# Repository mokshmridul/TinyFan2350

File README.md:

# Klipper TinyFan2350

A small Klipper fan / LED / thermistor controller based on the **Waveshare RP2350-Zero**, derived from [Gi7mo/TinyFan](https://github.com/Gi7mo/TinyFan).

|[• Build it](./Production)|[• Set it up](./Klipper)|[• Mount it](./Mount)|
|---|---|---|
|Order the PCB, parts list, soldering|Flashing, jumpers, wiring, Klipper config|Printable DIN rail mount, optional fan bridge|

## Features
- **5 fan ports** (JST-XH 4-pin) for 2-, 3- and 4-pin fans, 0.6A each
  - every fan has its own PWM output and tacho input -> independent speeds
  - per fan: mode jumper (**4P** = 4-pin PWM, **2/3** = switched GND) and voltage jumper (**VIN** or **5V**)
- **2 addressable LED ports** (JST-XH 3-pin), data level-shifted to 5V, VIN or 5V per port, 3A per connector
- **4 thermistor ports** (JST-XH 2-pin) on the RP2350 ADC
- **EXP header** with 4 free GPIOs (GP12-GP15)
- Inputs: **12/24V (VIN)** and **5V** for the fans and LEDs, each with a mini blade fuse (5A max, 3.75A continuous) and a
  reverse-polarity diode; no converters on board
- The RP2350-Zero is powered by its own **USB-C** cable, so the board cannot feed power back into the USB host
- All bottom-side SMD parts are **JLCPCB Basic** parts (cheap Economic assembly)
- 2 layers, 1 oz copper, black solder mask; SMD parts only on the bottom, THT only on the top; socketed MCU
- 100 x 65 mm, 4x M3 mounting holes (93 x 58 mm)
- Printable [DIN rail mount](./Mount) and an optional [fan bridge](./Mount#fan-bridge-optional) for a 40 mm cooling fan, run from one of the fan ports

## Files
|[Pinout](./Images/TinyFan2350_Pinout.png)|[Schematic](./Production/TinyFan2350_Schematic.pdf)|[Klipper config](./Klipper/TinyFan2350.cfg)|[KiCad project](./KiCad)|[Simulation](./Simulation)|[Pictures](./Images)|[Download](https://github.com/mokshmridul/TinyFan2350/releases/latest)|
|---|---|---|---|---|---|---|

## Notes
- Original TinyFan by [Gi7mo](https://github.com/Gi7mo/TinyFan), idea by [Rama](https://github.com/Ramalama2).
- Board revision **v1.3**: new tach inputs (series resistor, pass transistor and a capacitor at the pin instead of a
  diode), so the RP2350 sees a fan's low level properly and stays protected while a fan is switched; the unused D3
  pads are gone. See [Build it](./Production#v13-printed-on-the-board). It passes KiCad ERC/DRC and is
  simulated, but **it has not been built or tested yet**: read [Limits and safety](./Production#limits-and-safety) first.
- Release **v1.31**: the [schematic](./Production/TinyFan2350_Schematic.pdf) is redrawn on one page and is easier to
  read. The circuit and the board did not change, and the board still reads v1.3.

## License
GPL-3.0, the same as the original TinyFan. See [LICENSE](./LICENSE).

## Disclaimer
This project is provided on an "as-is" basis, without any warranty of any kind. I am not responsible for any damage, injury, loss or other issues caused by building or using it. If you choose to build or use this board, you do so entirely at your own risk.

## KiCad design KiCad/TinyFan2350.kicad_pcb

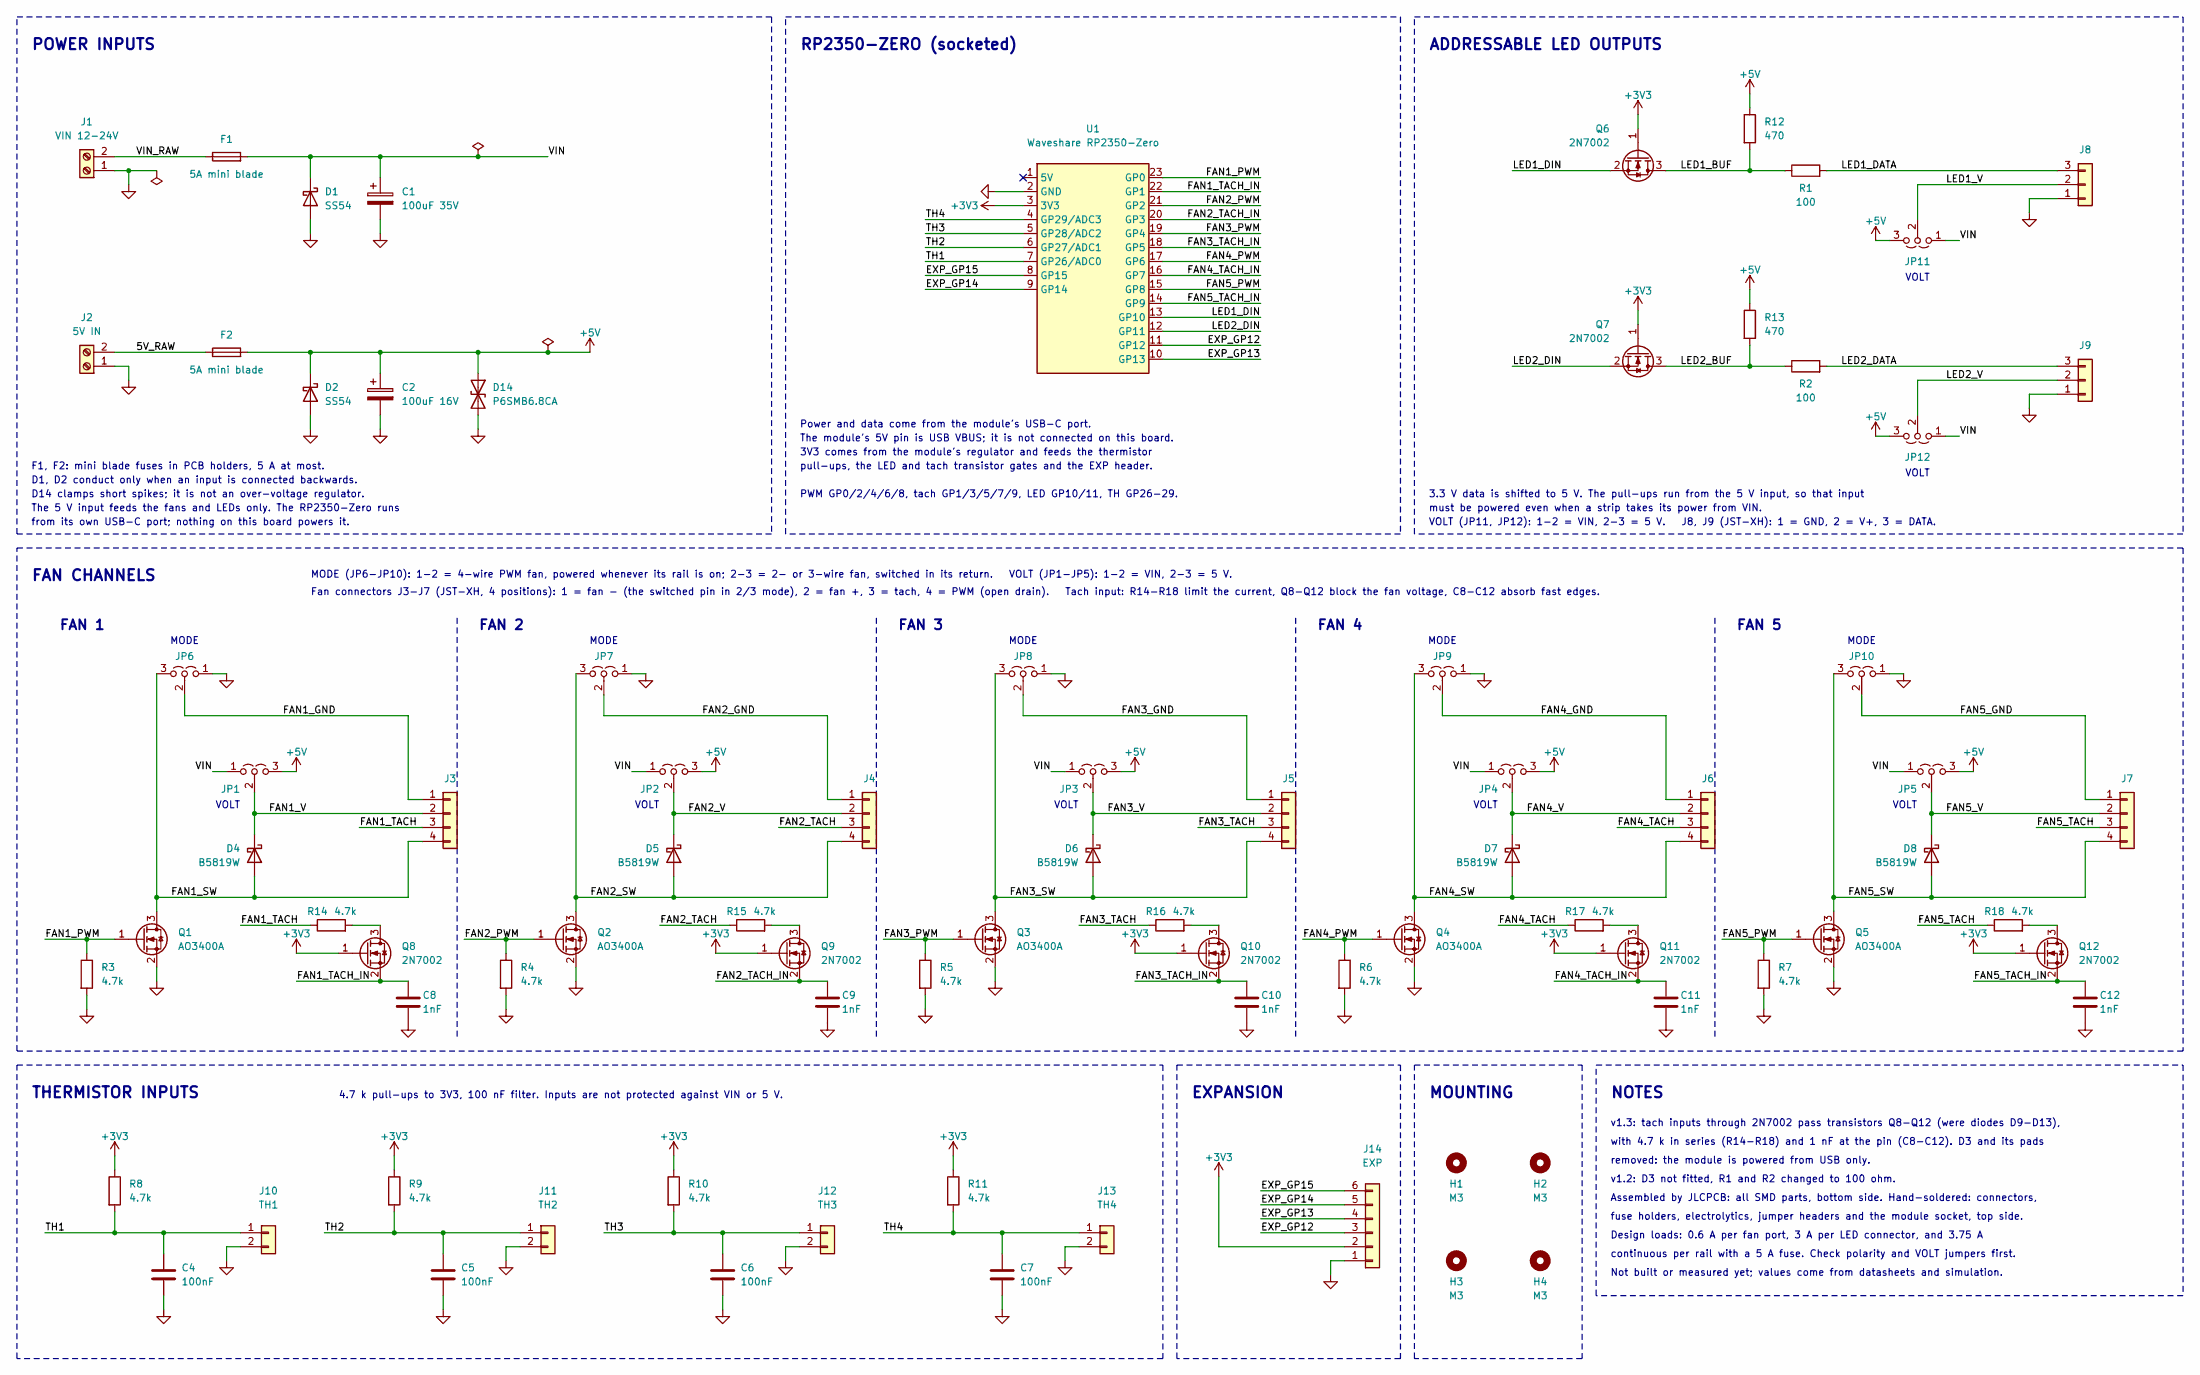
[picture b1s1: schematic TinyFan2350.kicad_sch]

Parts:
C1: 100uF 35V; CP_Radial_D8.0mm_P3.50mm
C2: 100uF 16V; CP_Radial_D6.3mm_P2.50mm
C4, C5, C6, C7: 100nF; C_0603_1608Metric
C8, C9, C10, C11, C12: 1nF; C_0603_1608Metric
D1, D2: SS54; D_SMA
D4, D5, D6, D7, D8: B5819W; D_SOD-123
D14: P6SMB6.8CA; D_SMB
F1, F2: 5A mini blade; Fuseholder_Blade_Mini_Keystone_3568
H1, H2, H3, H4: M3; MountingHole_3.2mm_M3
J1: VIN 12-24V; TerminalBlock_Phoenix_MKDS-1,5-2-5.08_1x02_P5.08mm_Horizont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
J2: 5V IN; TerminalBlock_Phoenix_MKDS-1,5-2-5.08_1x02_P5.08mm_Horizont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
J3: FAN1 (GND/V+/TACH/PWM); JST_XH_B4B-XH-A_1x04_P2.50mm_Vertical
J4: FAN2 (GND/V+/TACH/PWM); JST_XH_B4B-XH-A_1x04_P2.50mm_Vertical
J5: FAN3 (GND/V+/TACH/PWM); JST_XH_B4B-XH-A_1x04_P2.50mm_Vertical
J6: FAN4 (GND/V+/TACH/PWM); JST_XH_B4B-XH-A_1x04_P2.50mm_Vertical
J7: FAN5 (GND/V+/TACH/PWM); JST_XH_B4B-XH-A_1x04_P2.50mm_Vertical
J8: LED1 (GND/V+/DATA); JST_XH_B3B-XH-A_1x03_P2.50mm_Vertical
J9: LED2 (GND/V+/DATA); JST_XH_B3B-XH-A_1x03_P2.50mm_Vertical
J10: TH1; JST_XH_B2B-XH-A_1x02_P2.50mm_Vertical
J11: TH2; JST_XH_B2B-XH-A_1x02_P2.50mm_Vertical
J12: TH3; JST_XH_B2B-XH-A_1x02_P2.50mm_Vertical
J13: TH4; JST_XH_B2B-XH-A_1x02_P2.50mm_Vertical
J14: EXP; PinHeader_1x06_P2.54mm_Vertical
JP1: FAN1 V: VIN / 5V; PinHeader_1x03_P2.54mm_Vertical
JP2: FAN2 V: VIN / 5V; PinHeader_1x03_P2.54mm_Vertical
JP3: FAN3 V: VIN / 5V; PinHeader_1x03_P2.54mm_Vertical
JP4: FAN4 V: VIN / 5V; PinHeader_1x03_P2.54mm_Vertical
JP5: FAN5 V: VIN / 5V; PinHeader_1x03_P2.54mm_Vertical
JP6: FAN1 mode: 4P / 2-3P; PinHeader_1x03_P2.54mm_Vertical
JP7: FAN2 mode: 4P / 2-3P; PinHeader_1x03_P2.54mm_Vertical
JP8: FAN3 mode: 4P / 2-3P; PinHeader_1x03_P2.54mm_Vertical
JP9: FAN4 mode: 4P / 2-3P; PinHeader_1x03_P2.54mm_Vertical
JP10: FAN5 mode: 4P / 2-3P; PinHeader_1x03_P2.54mm_Vertical
JP11: LED1 V: VIN / 5V; PinHeader_1x03_P2.54mm_Vertical
JP12: LED2 V: VIN / 5V; PinHeader_1x03_P2.54mm_Vertical
Q1, Q2, Q3, Q4, Q5: AO3400A; SOT-23
Q6, Q7, Q8, Q9, Q10, Q11, Q12: 2N7002; SOT-23
R1, R2: 100; R_0603_1608Metric
R3, R4, R5, R6, R7, R8, R9, R10, R11, R14, R15, R16, R17, R18: 4.7k; R_0603_1608Metric
R12, R13: 470; R_0603_1608Metric
U1: Waveshare RP2350-Zero; Waveshare_RP2350-Zero_THT

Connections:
+3V3: J14.2, Q6.1 (G), Q7.1 (G), Q8.1 (G), Q9.1 (G), Q10.1 (G), Q11.1 (G), Q12.1 (G), R8.1, R9.1, R10.1, R11.1, U1.3 (3V3)
+5V: C2.1, D2.1 (K), D14.1 (A1), F2.2, JP1.3 (B), JP2.3 (B), JP3.3 (B), JP4.3 (B), JP5.3 (B), JP11.3 (B), JP12.3 (B), R12.1, R13.1
/5V_RAW: F2.1, J2.2
/EXP_GP12: J14.3, U1.11 (GP12)
/EXP_GP13: J14.4, U1.10 (GP13)
/EXP_GP14: J14.5, U1.9 (GP14)
/EXP_GP15: J14.6, U1.8 (GP15)
/FAN1_GND: J3.1, JP6.2 (C)
/FAN1_PWM: Q1.1 (G), R3.1, U1.23 (GP0)
/FAN1_SW: D4.2 (A), J3.4, JP6.3 (B), Q1.3 (D)
/FAN1_TACH: J3.3, R14.1
/FAN1_TACH_IN: C8.1, Q8.2 (S), U1.22 (GP1)
/FAN1_V: D4.1 (K), J3.2, JP1.2 (C)
/FAN2_GND: J4.1, JP7.2 (C)
/FAN2_PWM: Q2.1 (G), R4.1, U1.21 (GP2)
/FAN2_SW: D5.2 (A), J4.4, JP7.3 (B), Q2.3 (D)
/FAN2_TACH: J4.3, R15.1
/FAN2_TACH_IN: C9.1, Q9.2 (S), U1.20 (GP3)
/FAN2_V: D5.1 (K), J4.2, JP2.2 (C)
/FAN3_GND: J5.1, JP8.2 (C)
/FAN3_PWM: Q3.1 (G), R5.1, U1.19 (GP4)
/FAN3_SW: D6.2 (A), J5.4, JP8.3 (B), Q3.3 (D)
/FAN3_TACH: J5.3, R16.1
/FAN3_TACH_IN: C10.1, Q10.2 (S), U1.18 (GP5)
/FAN3_V: D6.1 (K), J5.2, JP3.2 (C)
/FAN4_GND: J6.1, JP9.2 (C)
/FAN4_PWM: Q4.1 (G), R6.1, U1.17 (GP6)
/FAN4_SW: D7.2 (A), J6.4, JP9.3 (B), Q4.3 (D)
/FAN4_TACH: J6.3, R17.1
/FAN4_TACH_IN: C11.1, Q11.2 (S), U1.16 (GP7)
/FAN4_V: D7.1 (K), J6.2, JP4.2 (C)
/FAN5_GND: J7.1, JP10.2 (C)
/FAN5_PWM: Q5.1 (G), R7.1, U1.15 (GP8)
/FAN5_SW: D8.2 (A), J7.4, JP10.3 (B), Q5.3 (D)
/FAN5_TACH: J7.3, R18.1
/FAN5_TACH_IN: C12.1, Q12.2 (S), U1.14 (GP9)
/FAN5_V: D8.1 (K), J7.2, JP5.2 (C)
/LED1_BUF: Q6.3 (D), R1.1, R12.2
/LED1_DATA: J8.3, R1.2
/LED1_DIN: Q6.2 (S), U1.13 (GP10)
/LED1_V: J8.2, JP11.2 (C)
/LED2_BUF: Q7.3 (D), R2.1, R13.2
/LED2_DATA: J9.3, R2.2
/LED2_DIN: Q7.2 (S), U1.12 (GP11)
/LED2_V: J9.2, JP12.2 (C)
/TH1: C4.1, J10.1, R8.2, U1.7 (GP26/ADC0)
/TH2: C5.1, J11.1, R9.2, U1.6 (GP27/ADC1)
/TH3: C6.1, J12.1, R10.2, U1.5 (GP28/ADC2)
/TH4: C7.1, J13.1, R11.2, U1.4 (GP29/ADC3)
/VIN: C1.1, D1.1 (K), F1.2, JP1.1 (A), JP2.1 (A), JP3.1 (A), JP4.1 (A), JP5.1 (A), JP11.1 (A), JP12.1 (A)
/VIN_RAW: F1.1, J1.2
GND: C1.2, C2.2, C4.2, C5.2, C6.2, C7.2, C8.2, C9.2, C10.2, C11.2, C12.2, D1.2 (A), D2.2 (A), D14.2 (A2), J1.1, J2.1, J8.1, J9.1, J10.2, J11.2, J12.2, J13.2, J14.1, JP6.1 (A), JP7.1 (A), JP8.1 (A), JP9.1 (A), JP10.1 (A), Q1.2 (S), Q2.2 (S), Q3.2 (S), Q4.2 (S), Q5.2 (S), R3.2, R4.2, R5.2, R6.2, R7.2, U1.2 (GND)
unnamed: Q8.3 (D), R14.2
unnamed: Q9.3 (D), R15.2
unnamed: Q10.3 (D), R16.2
unnamed: Q11.3 (D), R17.2
unnamed: Q12.3 (D), R18.2

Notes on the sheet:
POWER INPUTS
F1, F2: mini blade fuses in PCB holders, 5 A at most.
D1, D2 conduct only when an input is connected backwards.
D14 clamps short spikes; it is not an over-voltage regulator.
The 5 V input feeds the fans and LEDs only. The RP2350-Zero runs
from its own USB-C port; nothing on this board powers it.
RP2350-ZERO (socketed)
Power and data come from the module's USB-C port.
The module's 5V pin is USB VBUS; it is not connected on this board.
3V3 comes from the module's regulator and feeds the thermistor
pull-ups, the LED and tach transistor gates and the EXP header.
PWM GP0/2/4/6/8, tach GP1/3/5/7/9, LED GP10/11, TH GP26-29.
ADDRESSABLE LED OUTPUTS
VOLT
3.3 V data is shifted to 5 V. The pull-ups run from the 5 V input, so that input
must be powered even when a strip takes its power from VIN.
VOLT (JP11, JP12): 1-2 = VIN, 2-3 = 5 V. J8, J9 (JST-XH): 1 = GND, 2 = V+, 3 = DATA.
FAN CHANNELS
MODE (JP6-JP10): 1-2 = 4-wire PWM fan, powered whenever its rail is on; 2-3 = 2- or 3-wire fan, switched in its return. VOLT (JP1-JP5): 1-2 = VIN, 2-3 = 5 V.
Fan connectors J3-J7 (JST-XH, 4 positions): 1 = fan - (the switched pin in 2/3 mode), 2 = fan +, 3 = tach, 4 = PWM (open drain). Tach input: R14-R18 limit the current, Q8-Q12 block the fan voltage, C8-C12 absorb fast edges.
FAN 1
MODE
FAN 2
FAN 3
FAN 4
FAN 5
THERMISTOR INPUTS
4.7 k pull-ups to 3V3, 100 nF filter. Inputs are not protected against VIN or 5 V.
EXPANSION
MOUNTING
NOTES
v1.3: tach inputs through 2N7002 pass transistors Q8-Q12 (were diodes D9-D13),
with 4.7 k in series (R14-R18) and 1 nF at the pin (C8-C12). D3 and its pads
removed: the module is powered from USB only.
v1.2: D3 not fitted, R1 and R2 changed to 100 ohm.
Assembled by JLCPCB: all SMD parts, bottom side. Hand-soldered: connectors,
fuse holders, electrolytics, jumper headers and the module socket, top side.
Design loads: 0.6 A per fan port, 3 A per LED connector, and 3.75 A
continuous per rail with a 5 A fuse. Check polarity and VOLT jumpers first.
Not built or measured yet; values come from datasheets and simulation.

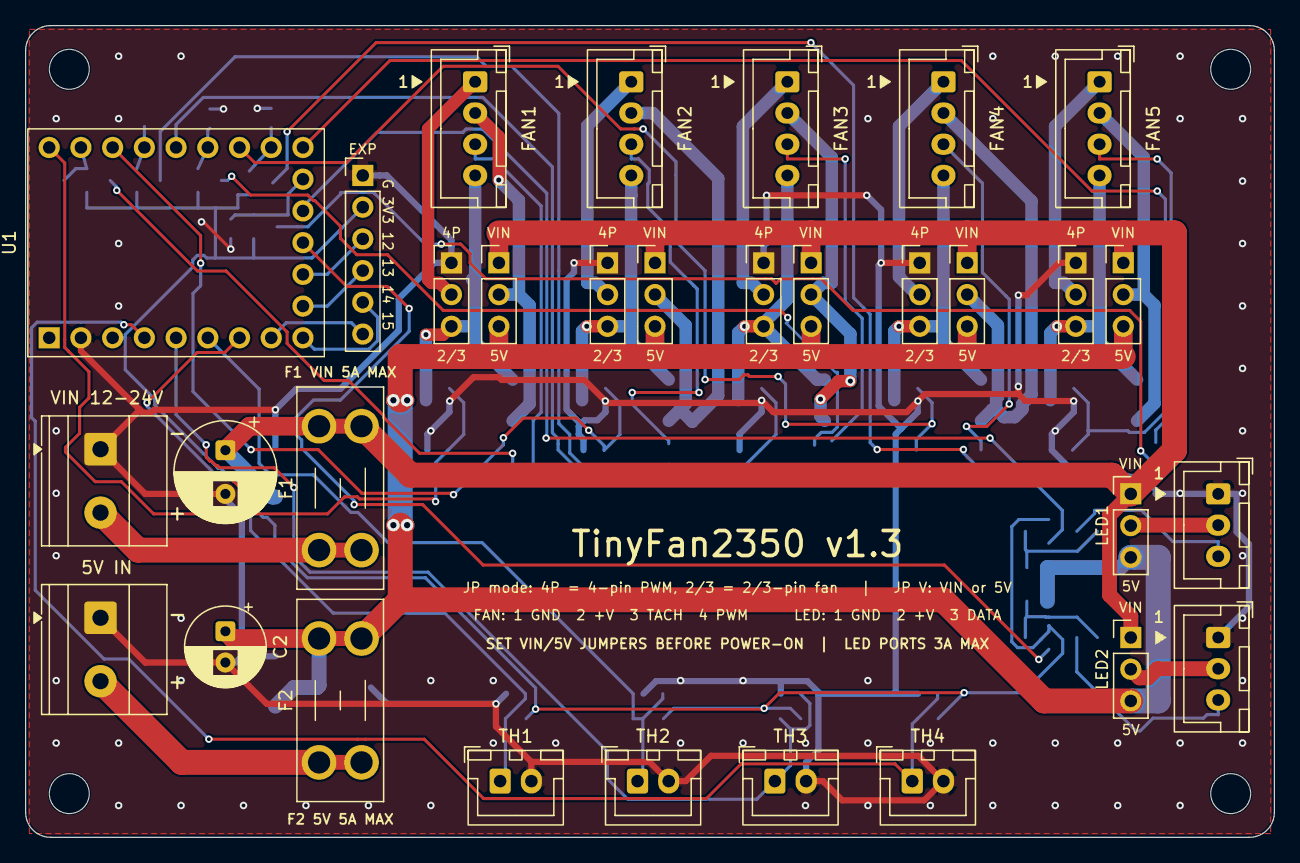
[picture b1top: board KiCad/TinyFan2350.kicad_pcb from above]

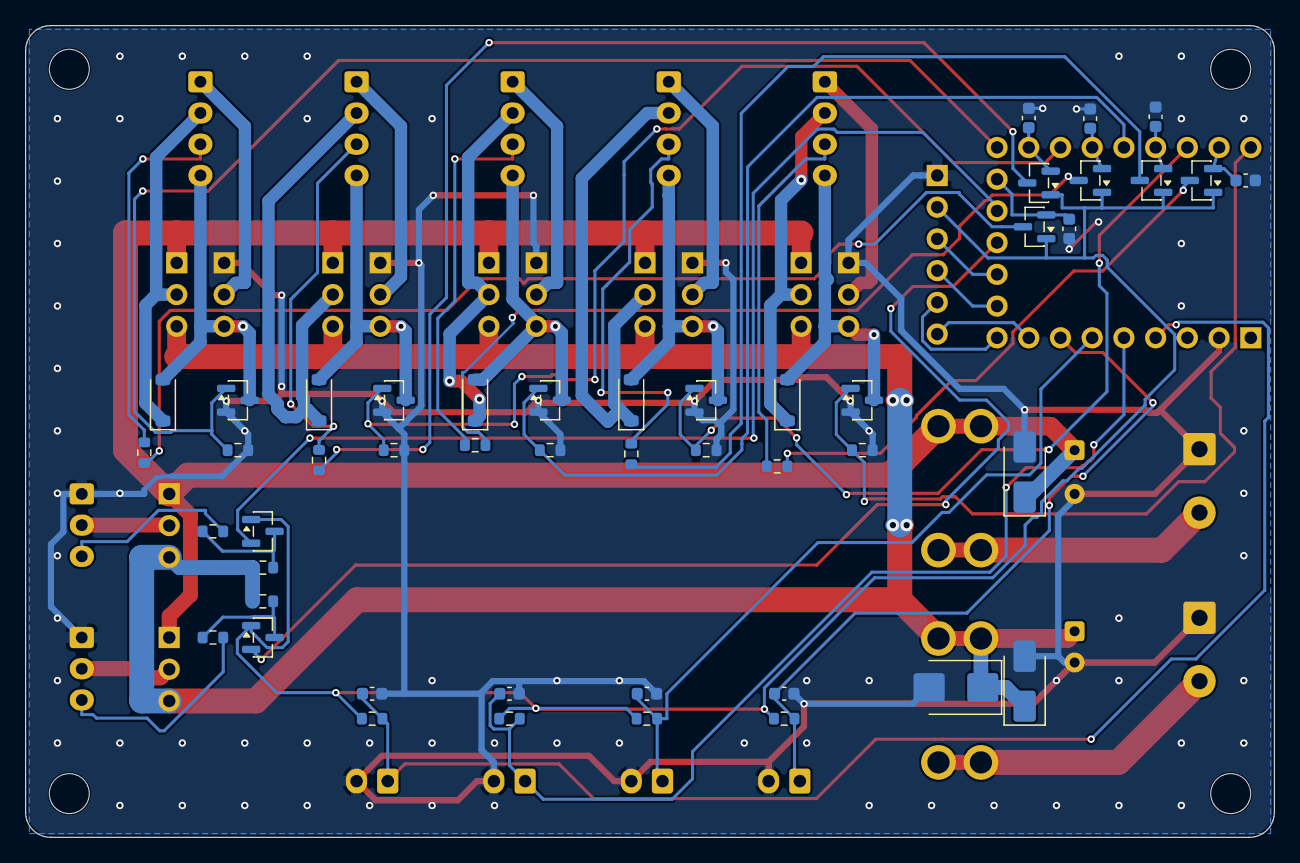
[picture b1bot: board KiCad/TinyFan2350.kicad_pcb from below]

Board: 2 copper layers, 100.0 x 65.0 mm, 82 parts (47 on the bottom side), 57 nets.

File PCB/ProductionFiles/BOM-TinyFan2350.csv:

Reference,Qty,Value,Footprint,LCSC,Note,Assembly
Q1 Q2 Q3 Q4 Q5,5,AO3400A,SOT-23,C20917,fan N-MOSFET 30V 5.7A,SMD bottom (JLC Basic)
Q6 Q7,2,2N7002,SOT-23,C8545,LED data level shifter 3.3V -> 5V,SMD bottom (JLC Basic)
D3 D4 D5 D6 D7 D8,6,B5819W SL,SOD-123,C8598,Schottky 40V 1A: fan flyback + MCU 5V feed,SMD bottom (JLC Basic)
D9 D10 D11 D12 D13,5,1N4148WS,SOD-323,C2128,tacho input protection,SMD bottom (JLC Basic)
D1 D2,2,SS54,SMA,C22452,"reverse-polarity crowbar, VIN and 5V inputs",SMD bottom (JLC Basic)
D14,1,P6SMB6.8CA,SMB,C78395,"TVS, over-voltage on the 5V input",SMD bottom (JLC Basic)
R3 R4 R5 R6 R7 R8 R9 R10 R11,9,4.7k 1%,0603,C23162,gate pull-downs + thermistor pull-ups,SMD bottom (JLC Basic)
R1 R2,2,330R 1%,0603,C23138,LED data series,SMD bottom (JLC Basic)
R12 R13,2,470R 1%,0603,C23179,LED data pull-up to 5V,SMD bottom (JLC Basic)
C4 C5 C6 C7,4,100nF 50V X7R,0603,C14663,thermistor filter,SMD bottom (JLC Basic)
C1,1,100uF 35V,Radial D8 P3.5,-,"VIN bulk, 105C",THT top
C2,1,100uF 16V,Radial D6.3 P2.5,-,"5V bulk, 105C",THT top
F1 F2,2,Keystone 3568,Mini blade holder,C5249699 (verify),mini blade (ATM) fuse holder,THT top
F1 F2 (fuse),2,ATM mini blade fuse 3-5A,-,-,"size to your load, 5A max",plug-in
J1 J2,2,Screw terminal 2P 5.08mm,"MKDS-1,5-2-5.08",-,power inputs,THT top
J3 J4 J5 J6 J7,5,JST B4B-XH-A,XH 4P vertical,C144395 (verify),fan ports,THT top
J8 J9,2,JST B3B-XH-A,XH 3P vertical,C144394 (verify),LED ports,THT top
J10 J11 J12 J13,4,JST B2B-XH-A,XH 2P vertical,C158012 (verify),thermistor ports,THT top
JP1-JP12,12,Pin header 1x3 2.54mm,1x03 P2.54,C2937625 (verify),jumpers,THT top
JP1-JP12 (caps),12,Jumper cap 2.54mm,-,-,one per jumper,plug-in
J14,1,Pin header 1x6 2.54mm,1x06 P2.54,C492405 (verify),EXP header,THT top
U1 socket,2,Female header 1x9 2.54mm 8.5mm,1x09 P2.54,C39576 (verify),"RP2350-Zero socket, side rows",THT top
U1 socket,1,Female header 1x5 2.54mm 8.5mm,1x05 P2.54,C50950 (verify),"RP2350-Zero socket, end row",THT top
U1,1,Waveshare RP2350-Zero (with pin headers),module,-,MCU,socketed
H1-H4,4,M3 screw / standoff,3.2mm hole,-,mounting,-

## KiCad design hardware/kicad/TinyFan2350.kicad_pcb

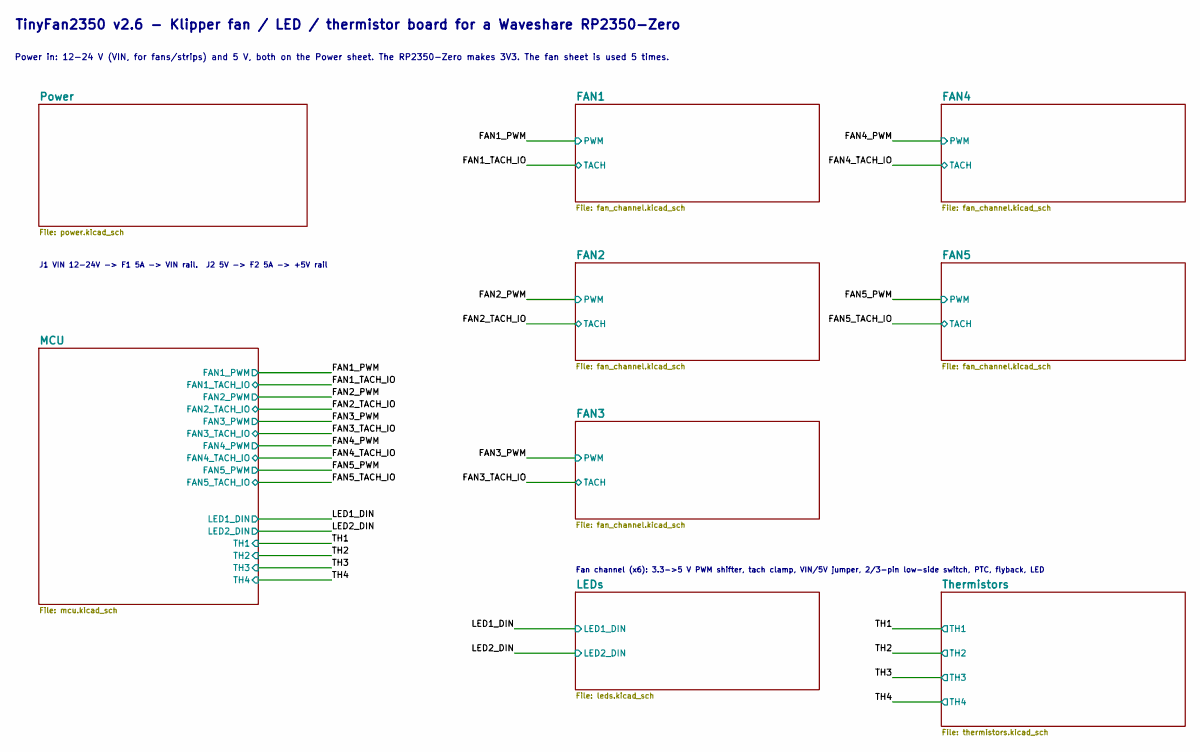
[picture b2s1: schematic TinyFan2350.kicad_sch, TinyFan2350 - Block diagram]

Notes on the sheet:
TinyFan2350 v2.6 - Klipper fan / LED / thermistor board for a Waveshare RP2350-Zero
Power in: 12-24 V (VIN, for fans/strips) and 5 V, both on the Power sheet. The RP2350-Zero makes 3V3. The fan sheet is used 5 times.
J1 VIN 12-24V -> F1 5A -> VIN rail. J2 5V -> F2 5A -> +5V rail
Fan channel (x6): 3.3->5 V PWM shifter, tach clamp, VIN/5V jumper, 2/3-pin low-side switch, PTC, flyback, LED

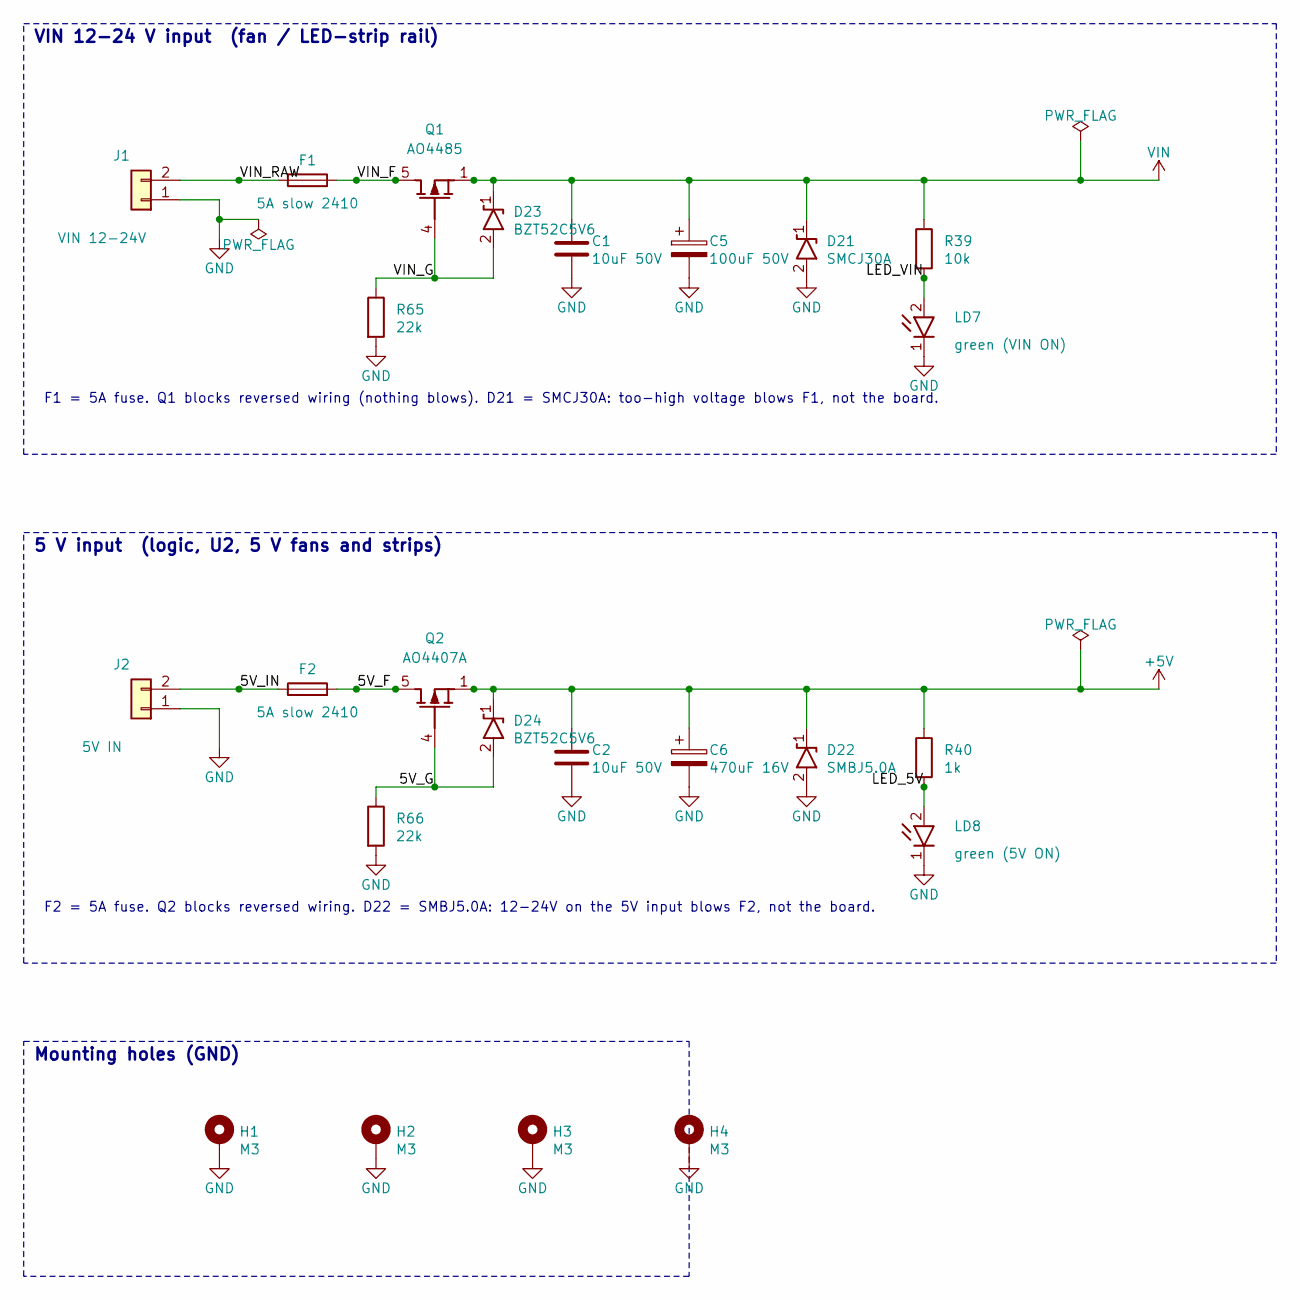
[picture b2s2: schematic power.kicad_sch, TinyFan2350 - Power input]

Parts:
C1, C2: 10uF 50V; C_1206_3216Metric; MPN CL31A106KBHNNNE; LCSC C13585
C5: 100uF 50V; CP_Radial_D8.0mm_P3.50mm_PlusLow; MPN 50YXF100MEFC8X11.5; LCSC C88728
C6: 470uF 16V; CP_Radial_D8.0mm_P3.50mm_PlusLow; MPN E2471M016D090RL; LCSC C2898814
D21: SMCJ30A; D_SMC; MPN SMCJ30A; LCSC C408374
D22: SMBJ5.0A; D_SMB; MPN SMBJ5.0A; LCSC C260407
D23, D24: BZT52C5V6; D_SOD-123; MPN BZT52C5V6; LCSC C2119
F1, F2: 5A slow 2410; Fuse_Littelfuse-NANO2-451_453; MPN 0452005.MRL; LCSC C66503
H1, H2, H3, H4: M3; MountingHole_3.2mm_M3_ISO7380_Pad
J1: VIN 12-24V; TerminalBlock_MKDS-1,5-2-5.08_EdgeEntry; MPN KF301-5.0-2P; LCSC C474881
J2: 5V IN; TerminalBlock_MKDS-1,5-2-5.08_EdgeEntry; MPN KF301-5.0-2P; LCSC C474881
LD7: green (VIN ON); LED_0805_2012Metric; MPN KT-0805G; LCSC C2297
LD8: green (5V ON); LED_0805_2012Metric; MPN KT-0805G; LCSC C2297
Q1: AO4485; SOIC-8_3.9x4.9mm_P1.27mm; MPN AO4485; LCSC C51499
Q2: AO4407A; SOIC-8_3.9x4.9mm_P1.27mm; MPN AO4407A; LCSC C2841482
R39: 10k; R_0805_2012Metric; MPN 0805W8F1002T5E; LCSC C17414
R40: 1k; R_0805_2012Metric; MPN 0805W8F1001T5E; LCSC C17513
R65, R66: 22k; R_0805_2012Metric; MPN 0805W8F2202T5E; LCSC C17560

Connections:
+5V: C2.1, C6.1, D22.1 (K), D24.1 (K), Q2.1 (S), Q2.2 (S), Q2.3 (S), R40.1; also elsewhere on the board
/Power/5V_F: F2.2, Q2.5 (D), Q2.6 (D), Q2.7 (D), Q2.8 (D)
/Power/5V_G: D24.2 (A), Q2.4 (G), R66.1
/Power/5V_IN: F2.1, J2.2
/Power/LED_5V: LD8.2 (A), R40.2
/Power/LED_VIN: LD7.2 (A), R39.2
/Power/VIN_F: F1.2, Q1.5 (D), Q1.6 (D), Q1.7 (D), Q1.8 (D)
/Power/VIN_G: D23.2 (A), Q1.4 (G), R65.1
/Power/VIN_RAW: F1.1, J1.2
GND: C1.2, C2.2, C5.2, C6.2, D21.2 (A), D22.2 (A), H1.1, H2.1, H3.1, H4.1, J1.1, J2.1, LD7.1 (K), LD8.1 (K), R65.2, R66.2; also elsewhere on the board
VIN: C1.1, C5.1, D21.1 (K), D23.1 (K), Q1.1 (S), Q1.2 (S), Q1.3 (S), R39.1; also elsewhere on the board

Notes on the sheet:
VIN 12-24 V input (fan / LED-strip rail)
5 V input (logic, U2, 5 V fans and strips)
Mounting holes (GND)
F1 = 5A fuse. Q1 blocks reversed wiring (nothing blows). D21 = SMCJ30A: too-high voltage blows F1, not the board.
F2 = 5A fuse. Q2 blocks reversed wiring. D22 = SMBJ5.0A: 12-24V on the 5V input blows F2, not the board.

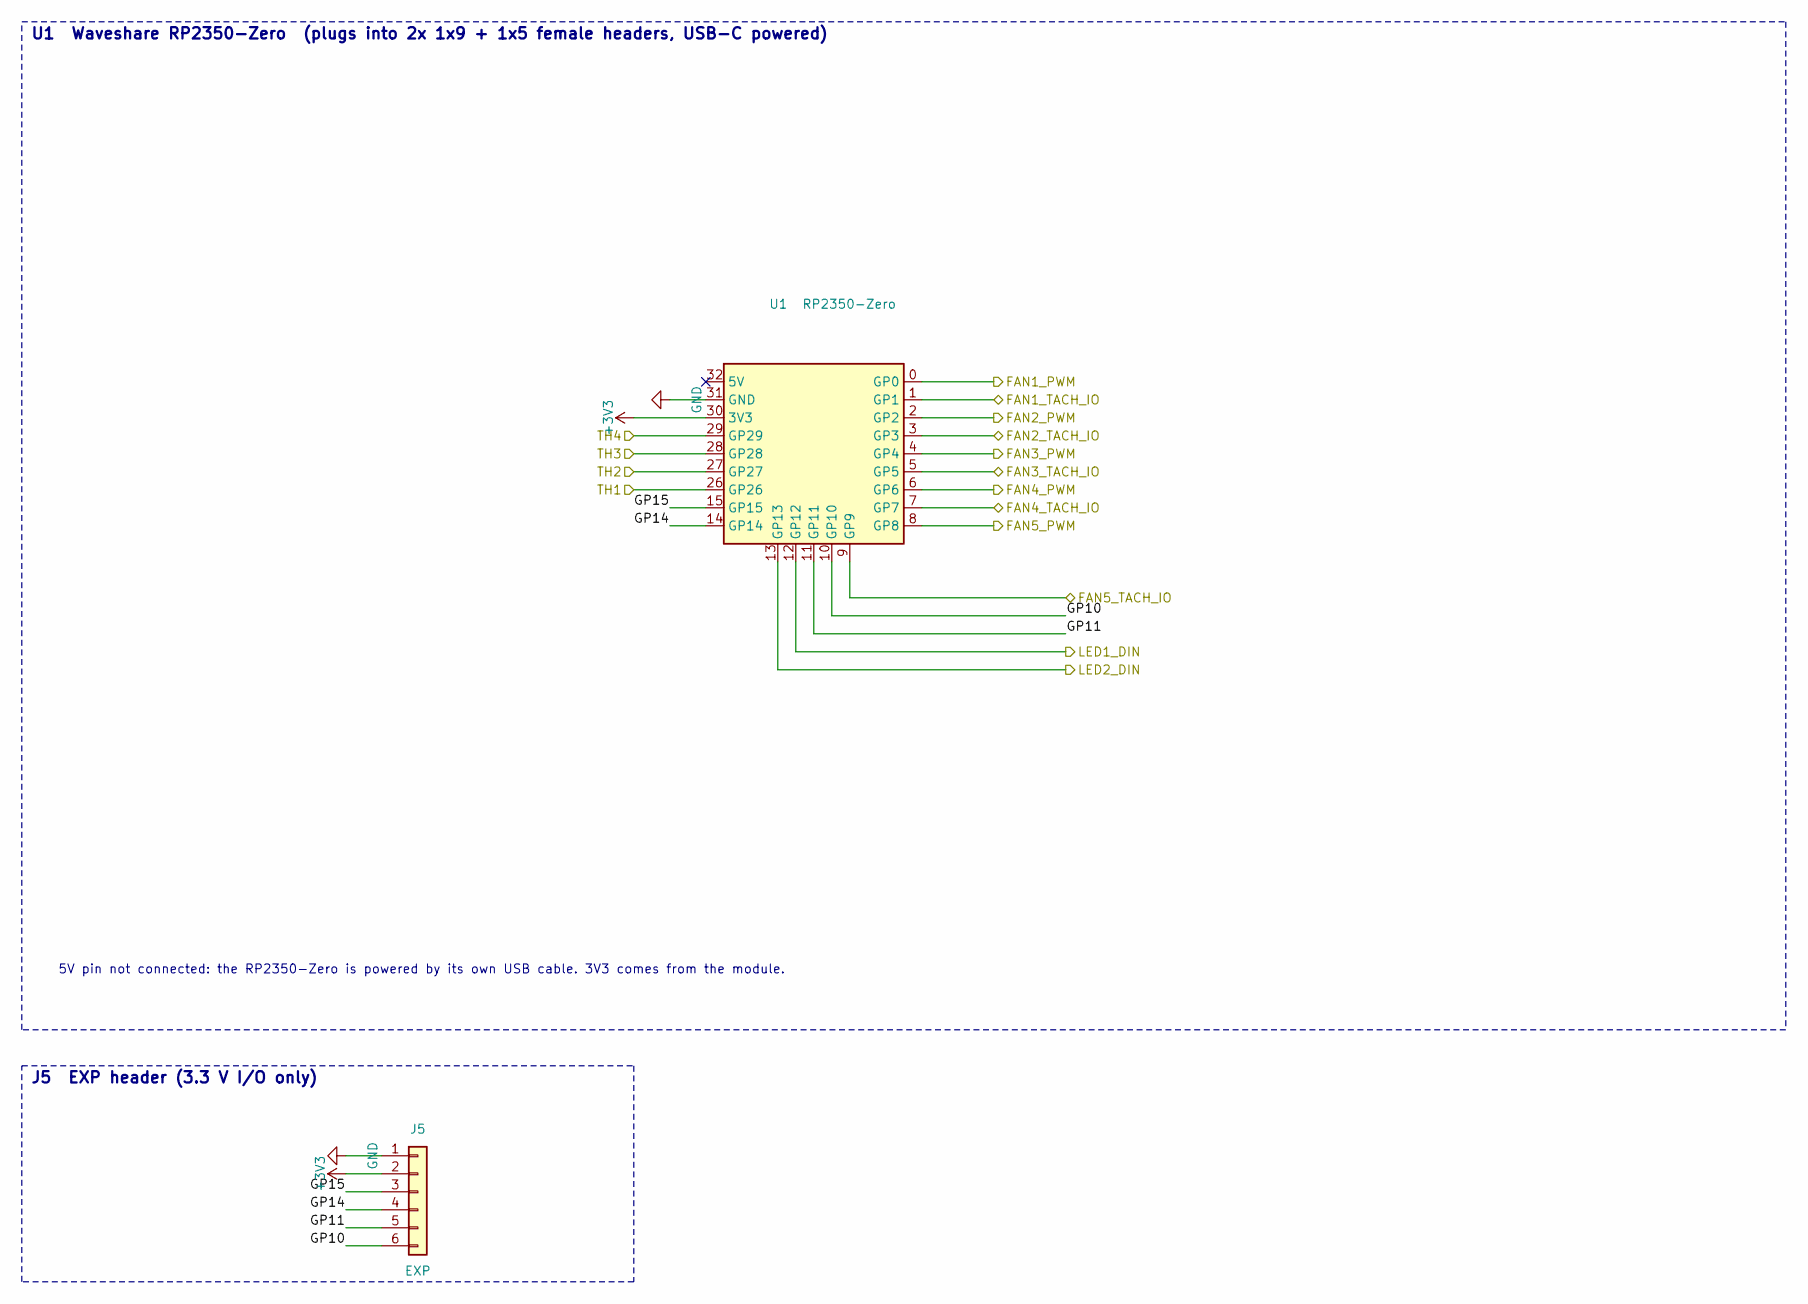
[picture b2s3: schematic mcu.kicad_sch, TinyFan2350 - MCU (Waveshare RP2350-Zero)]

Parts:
J5: EXP; PinHeader_1x06_P2.54mm_Vertical
U1: RP2350-Zero; RP2350-Zero_Socketed

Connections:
+3V3: J5.2, U1.30 (3V3); also elsewhere on the board
/FAN1_PWM: U1.0 (GP0); also elsewhere on the board
/FAN1_TACH_IO: U1.1 (GP1); also elsewhere on the board
/FAN2_PWM: U1.2 (GP2); also elsewhere on the board
/FAN2_TACH_IO: U1.3 (GP3); also elsewhere on the board
/FAN3_PWM: U1.4 (GP4); also elsewhere on the board
/FAN3_TACH_IO: U1.5 (GP5); also elsewhere on the board
/FAN4_PWM: U1.6 (GP6); also elsewhere on the board
/FAN4_TACH_IO: U1.7 (GP7); also elsewhere on the board
/FAN5_PWM: U1.8 (GP8); also elsewhere on the board
/FAN5_TACH_IO: U1.9 (GP9); also elsewhere on the board
/LED1_DIN: U1.12 (GP12); also elsewhere on the board
/LED2_DIN: U1.13 (GP13); also elsewhere on the board
/MCU/GP10: J5.6, U1.10 (GP10)
/MCU/GP11: J5.5, U1.11 (GP11)
/MCU/GP14: J5.4, U1.14 (GP14)
/MCU/GP15: J5.3, U1.15 (GP15)
/TH1: U1.26 (GP26); also elsewhere on the board
/TH2: U1.27 (GP27); also elsewhere on the board
/TH3: U1.28 (GP28); also elsewhere on the board
/TH4: U1.29 (GP29); also elsewhere on the board
GND: J5.1, U1.31 (GND); also elsewhere on the board

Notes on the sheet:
U1 Waveshare RP2350-Zero (plugs into 2x 1x9 + 1x5 female headers, USB-C powered)
5V pin not connected: the RP2350-Zero is powered by its own USB cable. 3V3 comes from the module.
J5 EXP header (3.3 V I/O only)

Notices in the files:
hardware/kicad/TinyFan2350.kicad_sch:
Derived from Gi7mo/TinyFan (GPL-3.0)
